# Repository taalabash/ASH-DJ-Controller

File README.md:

# ASH-DJ-Controller

ASH DJ controller is a basic dj controller for arduino mega 2560 , it basicly sends midi signals to the pc to control a dj software like Virtual-DJ 
this platform apears as generic midi controller in windows device manager (thanks to MOCO-LUFA)

the controller can handle :

* x40 keys with 16 of them that can change its function based on a mode key for each 8 with 5 modes for each groupe and there is a shift    key that can change the keys function in mode 5 (like the shift key for delete cue)
* x32 faders or potentiometer with 4 of them that changes its signals based on the mode switches (2 for each mode switch)
* x2 encoders
* x2 5-way mode switches (it can be used to switch between loops , hot cue , samplers , etc...)
* x2 shift keys (it can be used to delete hot cues )

there will be more featurs in future...

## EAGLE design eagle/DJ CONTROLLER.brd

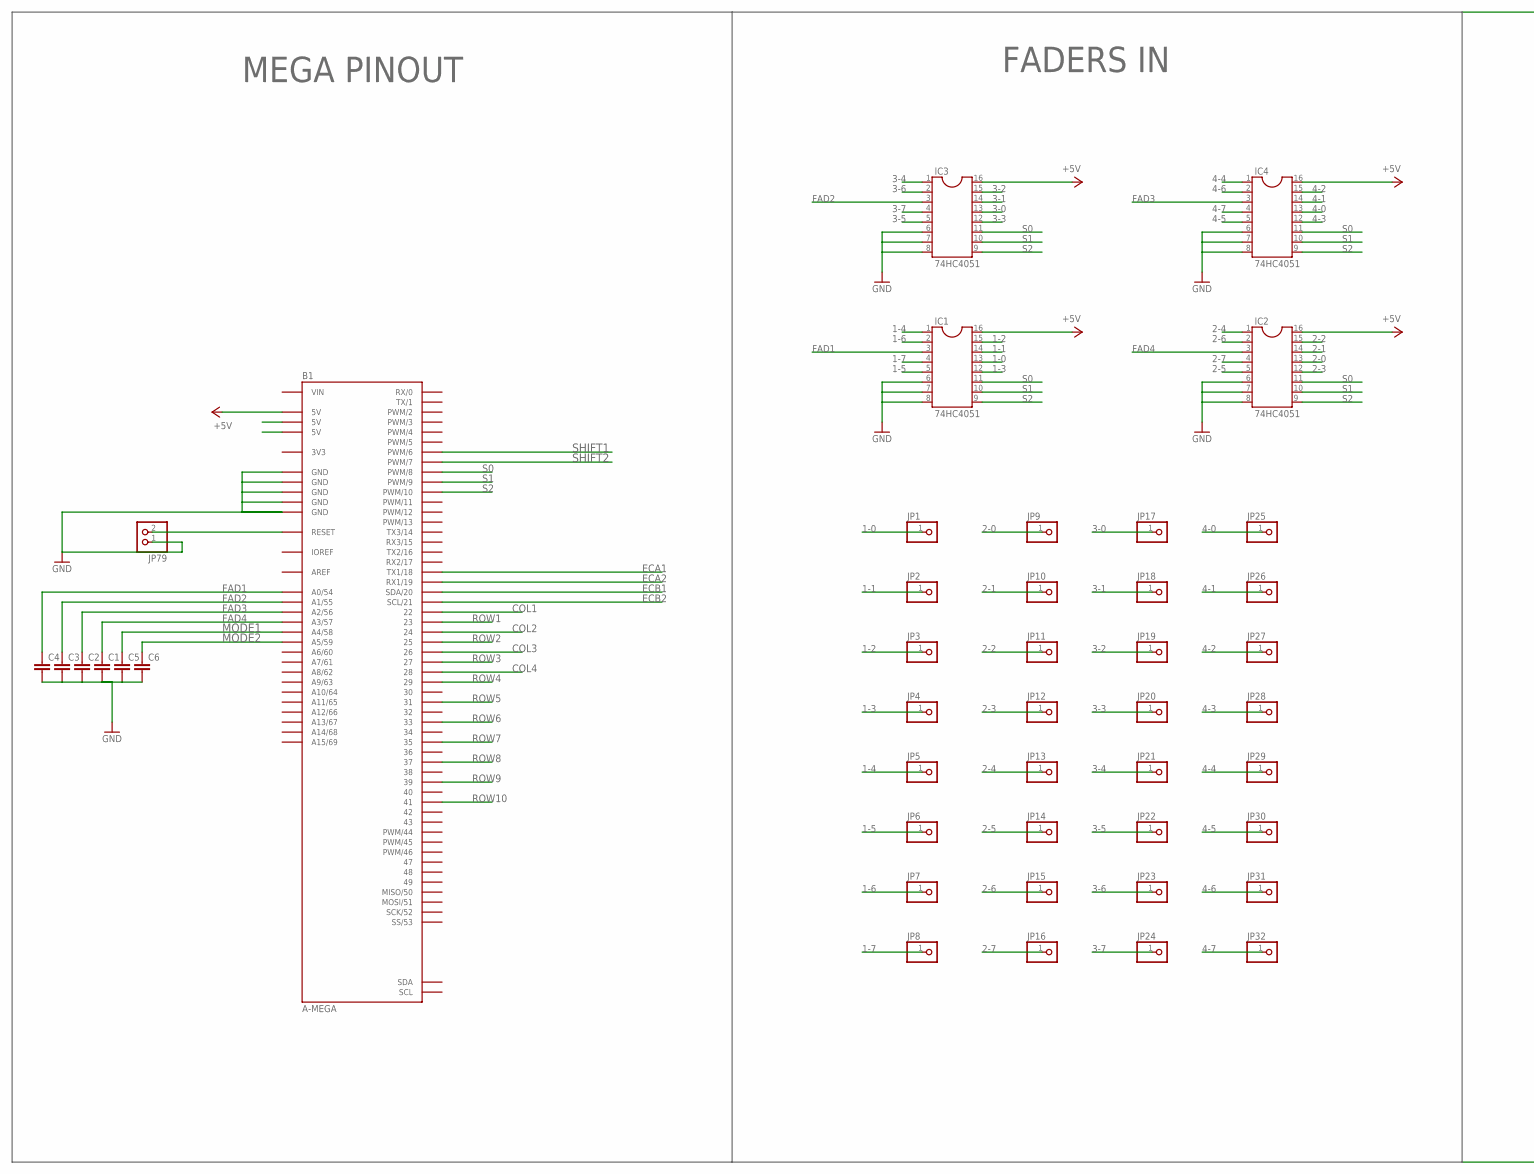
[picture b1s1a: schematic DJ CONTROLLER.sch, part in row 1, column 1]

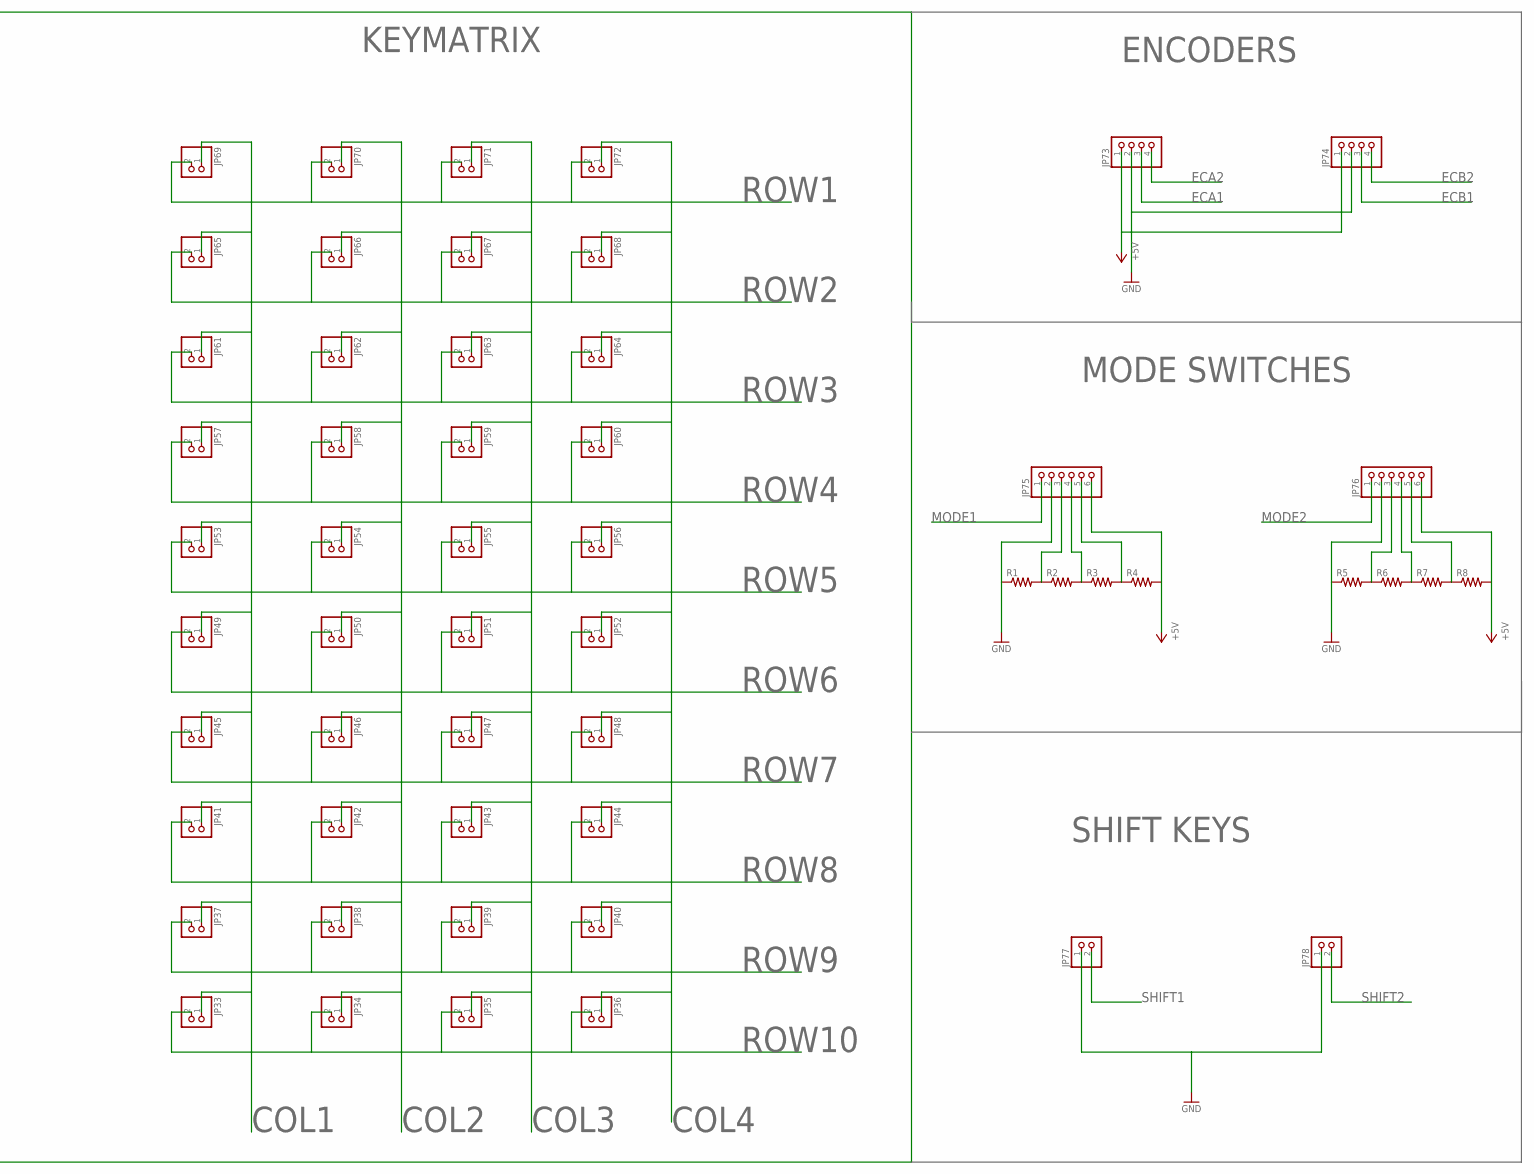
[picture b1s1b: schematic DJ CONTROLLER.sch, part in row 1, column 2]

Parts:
B1: A-MEGA
C1, C2, C3, C4, C5, C6: C-EU050-025X075; C050-025X075
IC1, IC2, IC3, IC4: 74HC4051; SOCKET-16
JP1, JP2, JP3, JP4, JP5, JP6, JP7, JP8, JP9, JP10, JP11, JP12, JP13, JP14, JP15, JP16, JP17, JP18, JP19, JP20, JP21, JP22, JP23, JP24, JP25, JP26, JP27, JP28, JP29, JP30, JP31, JP32: PINHD-1X1; 1X01
JP33, JP34, JP35, JP36, JP37, JP38, JP39, JP40, JP41, JP42, JP43, JP44, JP45, JP46, JP47, JP48, JP49, JP50, JP51, JP52, JP53, JP54, JP55, JP56, JP57, JP58, JP59, JP60, JP61, JP62, JP63, JP64, JP65, JP66, JP67, JP68, JP69, JP70, JP71, JP72, JP77, JP78, JP79: PINHD-1X2; 1X02
JP73, JP74: PINHD-1X4; 1X04
JP75, JP76: PINHD-1X6; 1X06
R1, R2, R3, R4, R5, R6, R7, R8: R-US_0204/7; 0204/7

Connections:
1-0: IC1.13, JP1.1
1-1: IC1.14, JP2.1
1-2: IC1.15, JP3.1
1-3: IC1.12, JP4.1
1-4: IC1.1, JP5.1
1-5: IC1.5, JP6.1
1-6: IC1.2, JP7.1
1-7: IC1.4, JP8.1
2-0: IC2.13, JP9.1
2-1: IC2.14, JP10.1
2-2: IC2.15, JP11.1
2-3: IC2.12, JP12.1
2-4: IC2.1, JP13.1
2-5: IC2.5, JP14.1
2-6: IC2.2, JP15.1
2-7: IC2.4, JP16.1
3-0: IC3.13, JP17.1
3-1: IC3.14, JP18.1
3-2: IC3.15, JP19.1
3-3: IC3.12, JP20.1
3-4: IC3.1, JP21.1
3-5: IC3.5, JP22.1
3-6: IC3.2, JP23.1
3-7: IC3.4, JP24.1
3V3: B1.3V3
4-0: IC4.13, JP25.1
4-1: IC4.14, JP26.1
4-2: IC4.15, JP27.1
4-3: IC4.12, JP28.1
4-4: IC4.1, JP29.1
4-5: IC4.5, JP30.1
4-6: IC4.2, JP31.1
4-7: IC4.4, JP32.1
+5V: B1.5V@1 (5V), IC1.16, IC2.16, IC3.16, IC4.16, JP73.1, JP74.1, JP75.6, JP76.6, R4.2, R8.2
AREF: B1.AREF
COL1: B1.22, JP33.1, JP37.1, JP41.1, JP45.1, JP49.1, JP53.1, JP57.1, JP61.1, JP65.1, JP69.1
COL2: B1.24, JP34.1, JP38.1, JP42.1, JP46.1, JP50.1, JP54.1, JP58.1, JP62.1, JP66.1, JP70.1
COL3: B1.26, JP35.1, JP39.1, JP43.1, JP47.1, JP51.1, JP55.1, JP59.1, JP63.1, JP67.1, JP71.1
COL4: B1.28, JP36.1, JP40.1, JP44.1, JP48.1, JP52.1, JP56.1, JP60.1, JP64.1, JP68.1, JP72.1
ECA1: B1.18 (TX1/18), JP73.3
ECA2: B1.19 (RX1/19), JP73.4
ECB1: B1.20 (SDA/20), JP74.3
ECB2: B1.21 (SCL/21), JP74.4
FAD1: B1.A0 (A0/54), C4.1, IC1.3
FAD2: B1.A1 (A1/55), C3.1, IC3.3
FAD3: B1.A2 (A2/56), C2.1, IC4.3
FAD4: B1.A3 (A3/57), C1.1, IC2.3
GND: B1.GND@1 (GND), B1.GND@2 (GND), B1.GND@3 (GND), B1.GND@4 (GND), B1.GND@5 (GND), C1.2, C2.2, C3.2, C4.2, C5.2, C6.2, IC1.6, IC1.7, IC1.8, IC2.6, IC2.7, IC2.8, IC3.6, IC3.7, IC3.8, IC4.6, IC4.7, IC4.8, JP73.2, JP74.2, JP75.2, JP76.2, JP77.1, JP78.1, JP79.1, R1.1, R5.1
IOREF: B1.IOREF
MODE1: B1.A4 (A4/58), C5.1, JP75.1
MODE2: B1.A5 (A5/59), C6.1, JP76.1
unnamed: JP76.3, R5.2, R6.1
unnamed: JP75.3, R1.2, R2.1
unnamed: JP75.4, R2.2, R3.1
unnamed: JP75.5, R3.2, R4.1
unnamed: JP76.4, R6.2, R7.1
unnamed: JP76.5, R7.2, R8.1
unnamed: B1.RST (RESET), JP79.2
ROW1: B1.23, JP69.2, JP70.2, JP71.2, JP72.2
ROW2: B1.25, JP65.2, JP66.2, JP67.2, JP68.2
ROW3: B1.27, JP61.2, JP62.2, JP63.2, JP64.2
ROW4: B1.29, JP57.2, JP58.2, JP59.2, JP60.2
ROW5: B1.31, JP53.2, JP54.2, JP55.2, JP56.2
ROW6: B1.33, JP49.2, JP50.2, JP51.2, JP52.2
ROW7: B1.35, JP45.2, JP46.2, JP47.2, JP48.2
ROW8: B1.37, JP41.2, JP42.2, JP43.2, JP44.2
ROW9: B1.39, JP37.2, JP38.2, JP39.2, JP40.2
ROW10: B1.41, JP33.2, JP34.2, JP35.2, JP36.2
S0: B1.8 (PWM/8), IC1.11, IC2.11, IC3.11, IC4.11
S1: B1.9 (PWM/9), IC1.10, IC2.10, IC3.10, IC4.10
S2: B1.10 (PWM/10), IC1.9, IC2.9, IC3.9, IC4.9
SHIFT1: B1.6 (PWM/6), JP77.2
SHIFT2: B1.7 (PWM/7), JP78.2
VIN: B1.VIN

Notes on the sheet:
FADERS IN
KEYMATRIX
ENCODERS
MEGA PINOUT
MODE SWITCHES
SHIFT KEYS

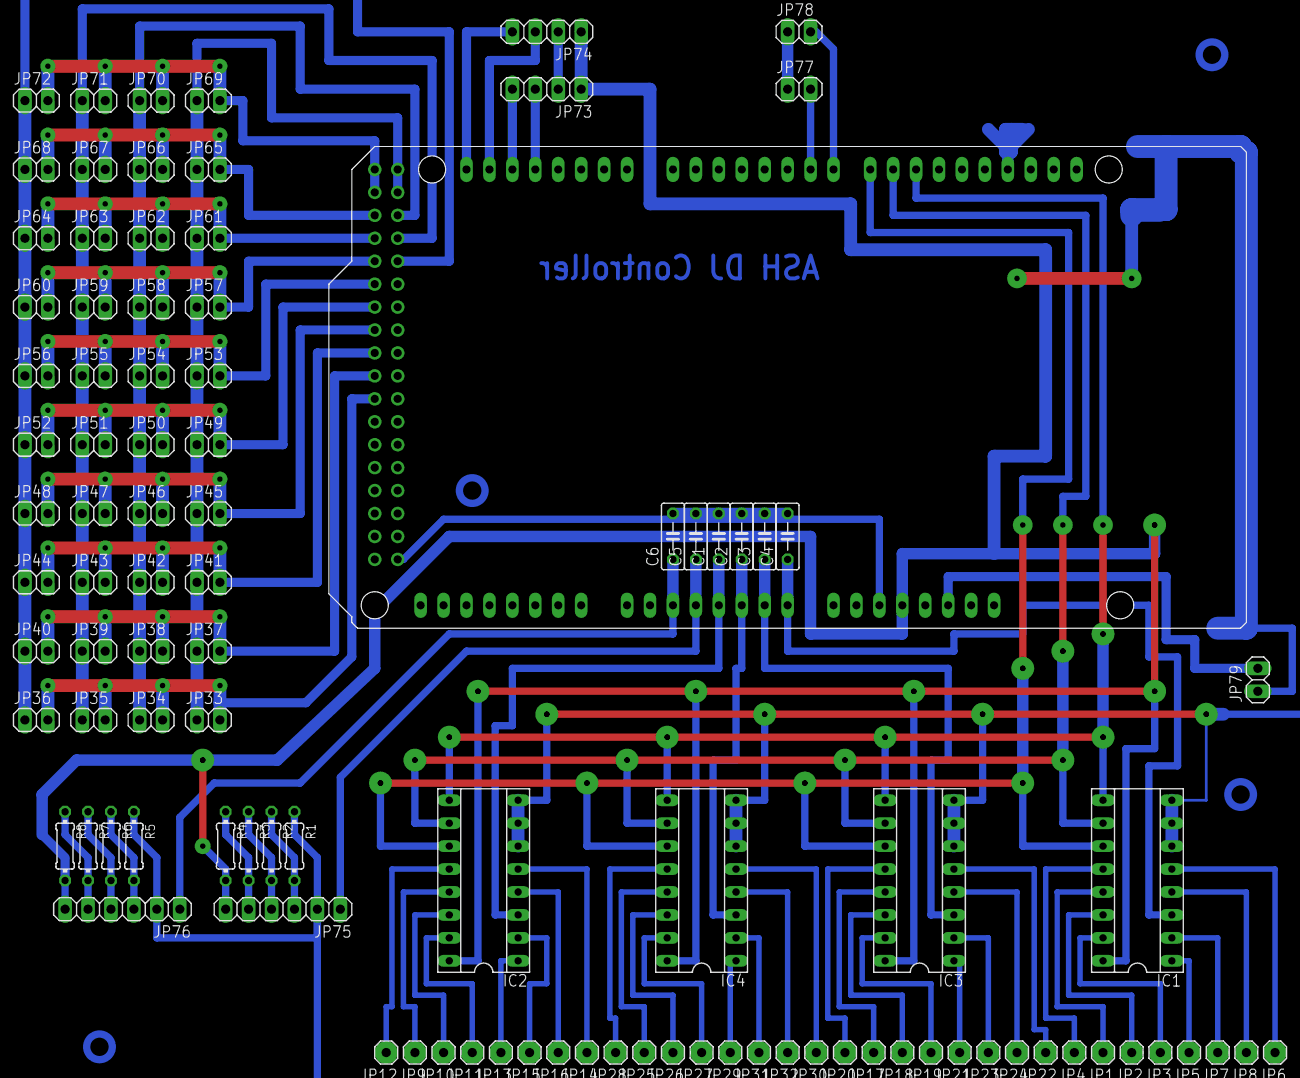
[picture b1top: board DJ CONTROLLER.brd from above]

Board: 2 copper layers, 98 parts (1 on the bottom side), 70 nets.

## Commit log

2016-09-10 Rename dj_controller_final.ino to firmware/dj_controller_final.ino
2016-09-10 Rename DJ CONTROLLER.brd to eagle/DJ CONTROLLER.brd
2016-09-10 Rename DJ CONTROLLER.sch to eagle/DJ CONTROLLER.sch
2016-09-17 added noise reduction capacitors for analog inputs
